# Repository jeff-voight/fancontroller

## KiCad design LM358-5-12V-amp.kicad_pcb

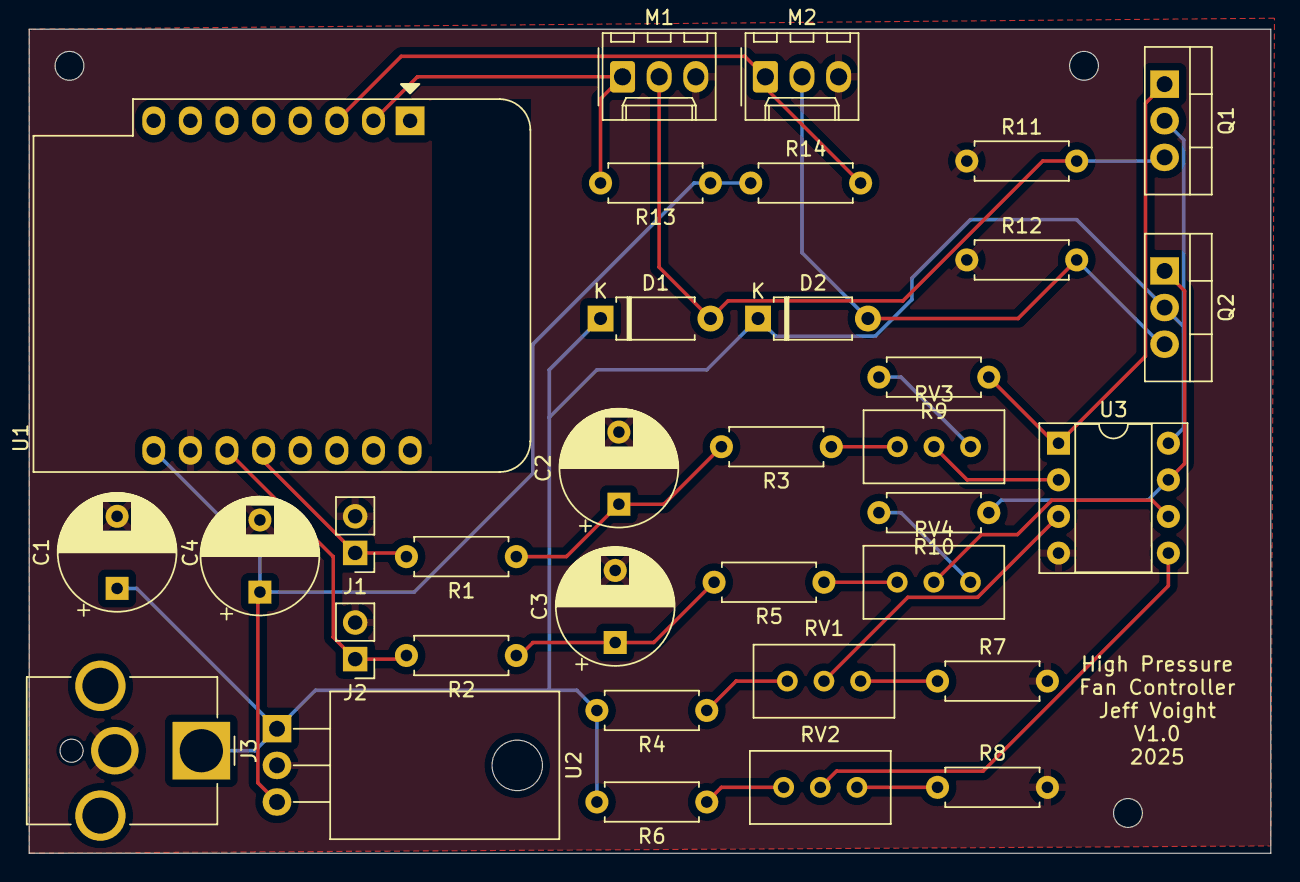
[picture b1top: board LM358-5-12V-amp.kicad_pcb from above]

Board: 2 copper layers, 86.1 x 57.2 mm, 34 parts (0 on the bottom side), 25 nets.

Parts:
C1, C4: 47uF; CP_Radial_D8.0mm_P5.00mm
C2, C3: 22pF; CP_Radial_D8.0mm_P5.00mm
D1, D2: D; D_A-405_P7.62mm_Horizontal
J1, J2: IN1; PinHeader_1x02_P2.54mm_Vertical
J3: Barrel_Jack; BarrelJack_CUI_PJ-063AH_Horizontal_CircularHoles
M1, M2: Fan_3pin; Molex_KK-254_AE-6410-03A_1x03_P2.54mm_Vertical
Q1, Q2: TIP120; TO-220-3_Vertical
R1, R2: 680; R_Axial_DIN0207_L6.3mm_D2.5mm_P7.62mm_Horizontal
R3, R5: 3k; R_Axial_DIN0207_L6.3mm_D2.5mm_P7.62mm_Horizontal
R4, R6: 6.8k; R_Axial_DIN0207_L6.3mm_D2.5mm_P7.62mm_Horizontal
R7, R8: 1.5k; R_Axial_DIN0207_L6.3mm_D2.5mm_P7.62mm_Horizontal
R9, R10: 20k; R_Axial_DIN0207_L6.3mm_D2.5mm_P7.62mm_Horizontal
R11, R12: 46k; R_Axial_DIN0207_L6.3mm_D2.5mm_P7.62mm_Horizontal
R13, R14: 10k; R_Axial_DIN0207_L6.3mm_D2.5mm_P7.62mm_Horizontal
RV1, RV2, RV3, RV4: 5k; Potentiometer_Bourns_3296W_Vertical
U1: WeMos_D1_mini; WEMOS_D1_mini_light
U2: L7805; TO-220-3_Horizontal_TabDown
U3: LM358; DIP-8_W7.62mm_Socket

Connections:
5VDC: C4.1, R13.1, R14.1, U1.9, U2.3
14VDC: C1.1, D1.1, D2.1, J3.1, Q1.2, Q2.2, R4.2, R6.2, U2.1, U3.8
GND: C1.2, C2.2, C3.2, C4.2, J1.2, J2.2, J3.2, M1.3, M2.3, R7.2, R8.2, R11.1, R12.1, U1.10, U2.2, U3.4
unnamed: C2.1, R1.1, R3.2
unnamed: C3.1, R2.1, R5.2
unnamed: D1.2, M1.2, Q1.3, R11.2
unnamed: D2.2, M2.2, Q2.3, R12.2
unnamed: Q1.1, R9.1, U3.1
unnamed: Q2.1, R10.1, U3.7
unnamed: R3.1, RV3.3
unnamed: R4.1, RV1.3
unnamed: R5.1, RV4.3
unnamed: R6.1, RV2.3
unnamed: R7.1, RV1.1
unnamed: R8.1, RV2.1
unnamed: R9.2, RV3.1
unnamed: R10.2, RV4.1
unnamed: RV1.2, U3.3
unnamed: RV2.2, U3.5
unnamed: RV3.2, U3.2
unnamed: RV4.2, U3.6
PWM1: J1.1, R1.2, U1.12
PWM2: J2.1, R2.2, U1.11
TACH1: M1.1, R13.2, U1.2
TACH2: M2.1, R14.2, U1.3

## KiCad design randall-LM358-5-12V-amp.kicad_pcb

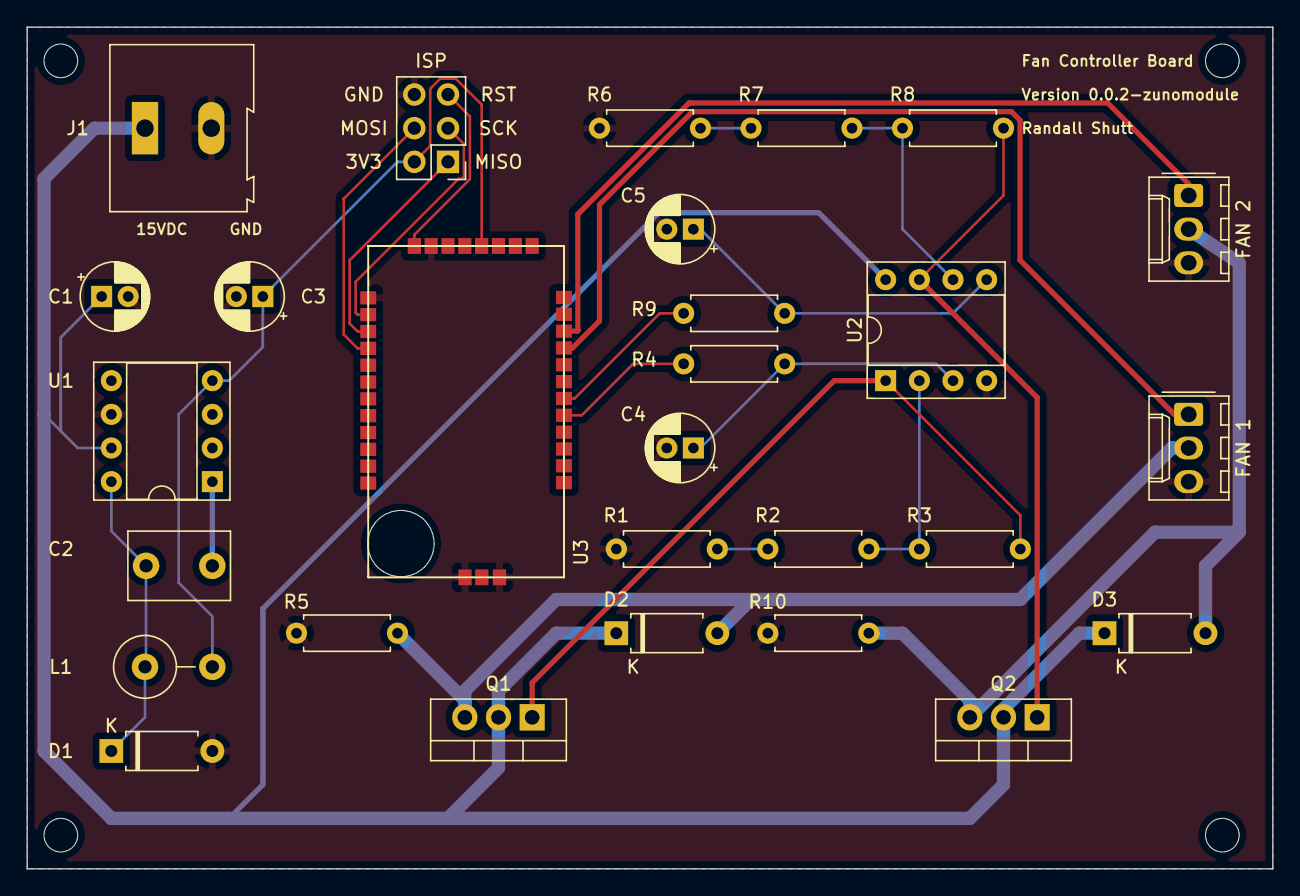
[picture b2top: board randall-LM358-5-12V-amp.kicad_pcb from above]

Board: 2 copper layers, 94.0 x 63.5 mm, 28 parts (0 on the bottom side), 23 nets.

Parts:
C1, C3, C4, C5: 100uF; CP_Radial_D5.0mm_P2.00mm
C2: 0.01uF; C_Disc_D7.5mm_W5.0mm_P5.00mm
D1: D_Schottky; D_A-405_P7.62mm_Horizontal
D2, D3: 1N1004; D_A-405_P7.62mm_Horizontal
FAN 1, FAN 2: Fan_3pin; Molex_KK-254_AE-6410-03A_1x03_P2.54mm_Vertical
ISP: AVR-ISP-6; PinHeader_2x03_P2.54mm_Vertical
J1: Power; TerminalBlock_Altech_AK300-2_P5.00mm
L1: 68uH; L_Axial_L14.0mm_D4.5mm_P5.08mm_Vertical_Fastron_LACC
Q1, Q2: TIP120; TO-220-3_Vertical_with_heatsink
R1, R6: 390; R_Axial_DIN0207_L6.3mm_D2.5mm_P7.62mm_Horizontal
R2, R7: 3.9k; R_Axial_DIN0207_L6.3mm_D2.5mm_P7.62mm_Horizontal
R3, R8: 15k; R_Axial_DIN0207_L6.3mm_D2.5mm_P7.62mm_Horizontal
R4, R9: 330; R_Axial_DIN0207_L6.3mm_D2.5mm_P7.62mm_Horizontal
R5, R10: 46k; R_Axial_DIN0207_L6.3mm_D2.5mm_P7.62mm_Horizontal
U1: LM2674M-3.3; DIP-8_W7.62mm_Socket
U2: LM358; DIP-8_W7.62mm_Socket
U3: Z-Uno-Module; Z-UNO Module

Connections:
3V3DC: C3.1, ISP.2, L1.2, U1.4, U3.26
15VDC: C1.1, D2.1, D3.1, J1.1, Q1.2, Q2.2, U1.7, U2.8
GND: C1.2, C3.2, C4.2, C5.2, D1.2, FAN 1.3, FAN 2.3, ISP.6, J1.2, R1.2, R5.1, R6.2, R10.1, U1.6, U2.4, U3.29, U3.31, U3.32, U3.34
MISO: ISP.1, U3.1
MOSI: ISP.4, U3.2
unnamed: C2.1, D1.1, L1.1, U1.8
unnamed: C2.2, U1.1
unnamed: C4.1, R4.1, U2.3
unnamed: C5.1, R9.1, U2.5
unnamed: D2.2, FAN 1.2, Q1.3, R5.2
unnamed: D3.2, FAN 2.2, Q2.3, R10.2
unnamed: Q1.1, R3.1, U2.1
unnamed: Q2.1, R8.1, U2.7
unnamed: R1.1, R2.2
unnamed: R2.1, R3.2, U2.2
unnamed: R6.1, R7.2
unnamed: R7.1, R8.2, U2.6
PWM1: R4.2, U3.13
PWM2: R9.2, U3.14
RST: ISP.5, U3.30
SCK: ISP.3, U3.0
TACH1: FAN 1.1, U3.17
TACH2: FAN 2.1, U3.18

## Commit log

2021-03-19 init
2021-03-20 added trim pots and TO220 transistor
2021-03-27 different voltage?
2021-04-15 This is my stuff
2021-04-15 Update gitignore
2021-04-25 Footprint PCB Time
2021-04-25 Ok cool
2021-04-25 Added Arduino code
2021-04-26 This is it, make no mistake about it
2021-04-26 Added zuno module
2021-04-26 Ok this is probably wrong due to Via use?
2021-04-26 traces on top and aligned
2021-04-27 added drill holes and re-arrange board
2021-04-27 version number
2021-04-27 Ok added an antenna and some keepouts and rerouted a trace or two:
2021-05-04 Updated with P/Ns where necessary
2021-05-04 Updating P/N
2021-05-05 Im not sure what changed here :)
2025-09-30 d1mini
2025-09-30 D1mini (#1)
    * This is my stuff
    * Update gitignore
    * Delete LM358-5-12V-amp.kicad_pcb-bak
    * Delete LM358-5-12V-amp.sch-bak
    * Delete .DS_Store
    * Footprint PCB Time
2025-10-30 Board layout. Still missing mounting holes.
2025-10-30 Mounting holes
